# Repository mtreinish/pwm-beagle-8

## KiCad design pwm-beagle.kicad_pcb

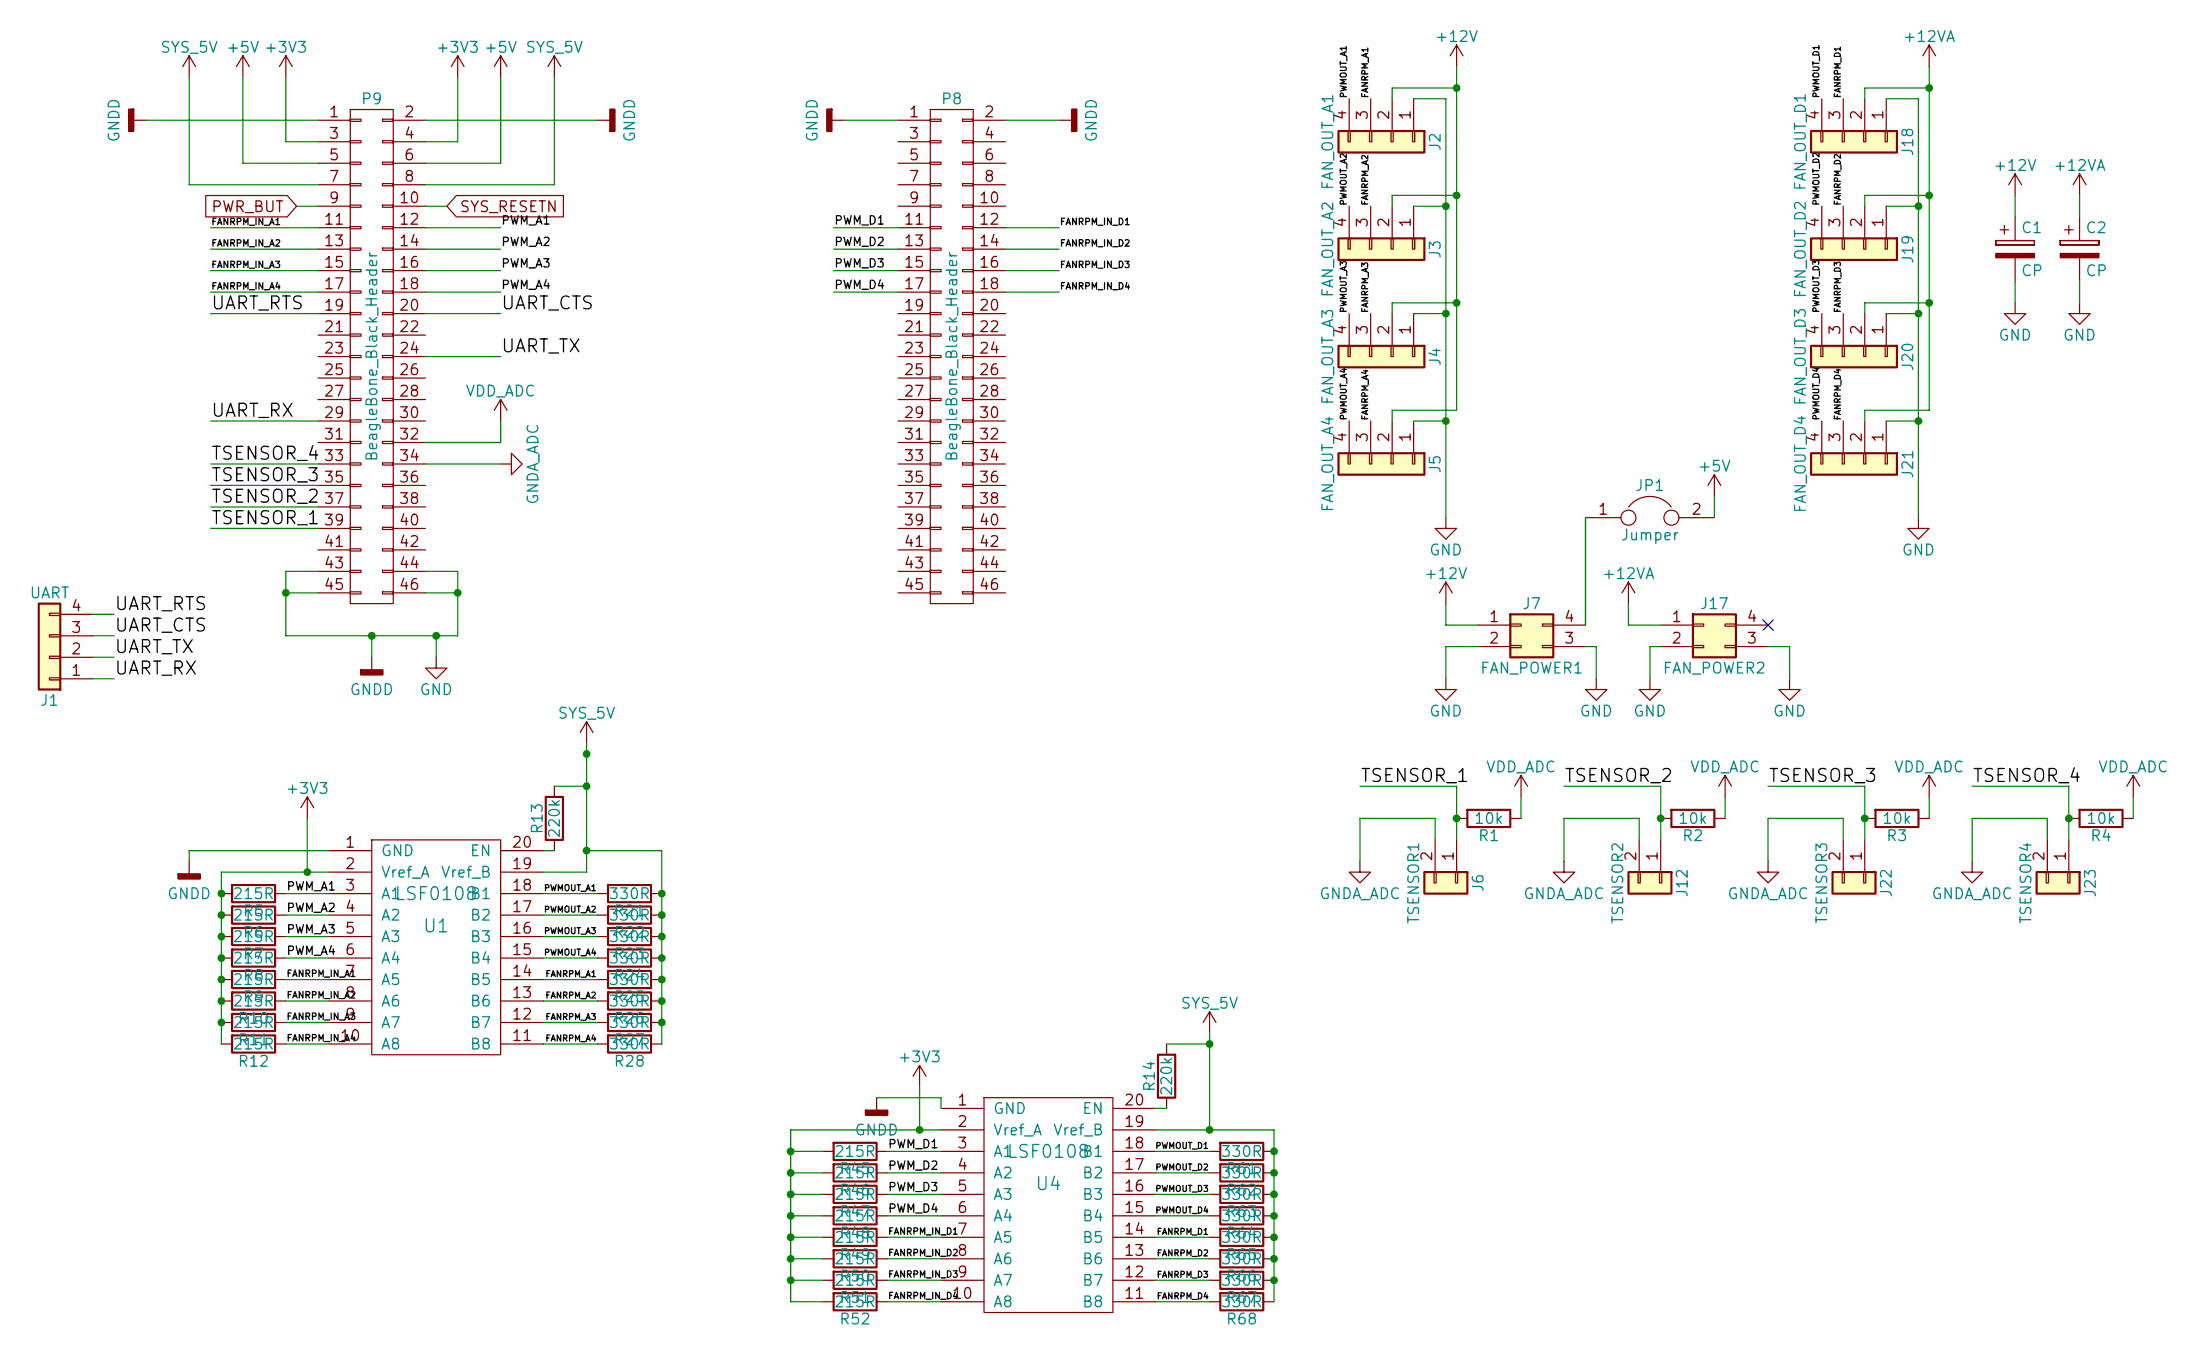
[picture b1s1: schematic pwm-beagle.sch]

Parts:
C1, C2: CP; CP_Elec_5x4.5
J1: UART; Molex_KK-6410-04_04x2.54mm_Straight
J2: FAN_OUT_A1; Molex_KK-6410-04_04x2.54mm_Straight
J3: FAN_OUT_A2; Molex_KK-6410-04_04x2.54mm_Straight
J4: FAN_OUT_A3; Molex_KK-6410-04_04x2.54mm_Straight
J5: FAN_OUT_A4; Molex_KK-6410-04_04x2.54mm_Straight
J6: TSENSOR1; Molex_KK-41791-02_02x3.96mm_Straight
J7: FAN_POWER1; conn_hdd_15-24-4449
J12: TSENSOR2; Molex_KK-41791-02_02x3.96mm_Straight
J17: FAN_POWER2; conn_hdd_15-24-4449
J18: FAN_OUT_D1; Molex_KK-6410-04_04x2.54mm_Straight
J19: FAN_OUT_D2; Molex_KK-6410-04_04x2.54mm_Straight
J20: FAN_OUT_D3; Molex_KK-6410-04_04x2.54mm_Straight
J21: FAN_OUT_D4; Molex_KK-6410-04_04x2.54mm_Straight
J22: TSENSOR3; Molex_KK-41791-02_02x3.96mm_Straight
J23: TSENSOR4; Molex_KK-41791-02_02x3.96mm_Straight
JP1: Jumper; Pin_Header_Straight_1x02_Pitch2.00mm
P8, P9: BeagleBone_Black_Header; Socket_BeagleBone_Black
R1, R2, R3, R4: 10k; R_0805_HandSoldering
R5, R6, R7, R8, R9, R10, R11, R12, R45, R46, R47, R48, R49, R50, R51, R52: 215R; R_0603_HandSoldering
R13, R14: 220k; R_0805_HandSoldering
R21, R22, R23, R24, R25, R26, R27, R28, R61, R62, R63, R64, R65, R66, R67, R68: 330R; R_0603_HandSoldering
U1, U4: LSF0108; SSOP-20

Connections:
+3V3: P9.3, P9.4, R5.2, R6.2, R7.2, R8.2, R9.2, R10.2, R11.2, R12.2, R45.2, R46.2, R47.2, R48.2, R49.2, R50.2, R51.2, R52.2, U1.2 (Vref_A), U4.2 (Vref_A)
+5V: JP1.2, P9.5, P9.6
+12V: C1.1, J2.2, J3.2, J4.2, J5.2, J7.1
+12VA: C2.1, J17.1, J18.2, J19.2, J20.2, J21.2
/FANRPM_A1: J2.3, R25.2, U1.14 (B5)
/FANRPM_A2: J3.3, R26.2, U1.13 (B6)
/FANRPM_A3: J4.3, R27.2, U1.12 (B7)
/FANRPM_A4: J5.3, R28.2, U1.11 (B8)
/FANRPM_D1: J18.3, R65.2, U4.14 (B5)
/FANRPM_D2: J19.3, R66.2, U4.13 (B6)
/FANRPM_D3: J20.3, R67.2, U4.12 (B7)
/FANRPM_D4: J21.3, R68.2, U4.11 (B8)
/FANRPM_IN_A1: P9.11, R9.1, U1.7 (A5)
/FANRPM_IN_A2: P9.13, R10.1, U1.8 (A6)
/FANRPM_IN_A3: P9.15, R11.1, U1.9 (A7)
/FANRPM_IN_A4: P9.17, R12.1, U1.10 (A8)
/FANRPM_IN_D1: P8.12, R49.1, U4.7 (A5)
/FANRPM_IN_D2: P8.14, R50.1, U4.8 (A6)
/FANRPM_IN_D3: P8.16, R51.1, U4.9 (A7)
/FANRPM_IN_D4: P8.18, R52.1, U4.10 (A8)
/PWMOUT_A1: J2.4, R21.2, U1.18 (B1)
/PWMOUT_A2: J3.4, R22.2, U1.17 (B2)
/PWMOUT_A3: J4.4, R23.2, U1.16 (B3)
/PWMOUT_A4: J5.4, R24.2, U1.15 (B4)
/PWMOUT_D1: J18.4, R61.2, U4.18 (B1)
/PWMOUT_D2: J19.4, R62.2, U4.17 (B2)
/PWMOUT_D3: J20.4, R63.2, U4.16 (B3)
/PWMOUT_D4: J21.4, R64.2, U4.15 (B4)
/PWM_A1: P9.12, R5.1, U1.3 (A1)
/PWM_A2: P9.14, R6.1, U1.4 (A2)
/PWM_A3: P9.16, R7.1, U1.5 (A3)
/PWM_A4: P9.18, R8.1, U1.6 (A4)
/PWM_D1: P8.11, R45.1, U4.3 (A1)
/PWM_D2: P8.13, R46.1, U4.4 (A2)
/PWM_D3: P8.15, R47.1, U4.5 (A3)
/PWM_D4: P8.17, R48.1, U4.6 (A4)
/TSENSOR_1: J6.1, P9.39, R1.2
/TSENSOR_2: J12.1, P9.37, R2.2
/TSENSOR_3: J22.1, P9.35, R3.2
/TSENSOR_4: J23.1, P9.33, R4.2
/UART_CTS: J1.3, P9.20
/UART_RTS: J1.4, P9.19
/UART_RX: J1.1, P9.29
/UART_TX: J1.2, P9.24
GND: C1.2, C2.2, J2.1, J3.1, J4.1, J5.1, J7.2, J7.3, J17.2, J17.3, J18.1, J19.1, J20.1, J21.1, P8.1, P8.2, P9.1, P9.2, P9.43, P9.44, P9.45, P9.46, U1.1 (GND), U4.1 (GND)
GNDA_ADC: J6.2, J12.2, J22.2, J23.2, P9.34
unnamed: J7.4, JP1.1
unnamed: R13.1, U1.20 (EN)
unnamed: R14.1, U4.20 (EN)
PWR_BUT: P9.9
SYS_5V: P9.7, P9.8, R13.2, R14.2, R21.1, R22.1, R23.1, R24.1, R25.1, R26.1, R27.1, R28.1, R61.1, R62.1, R63.1, R64.1, R65.1, R66.1, R67.1, R68.1, U1.19 (Vref_B), U4.19 (Vref_B)
SYS_RESETN: P9.10
VDD_ADC: P9.32, R1.1, R2.1, R3.1, R4.1

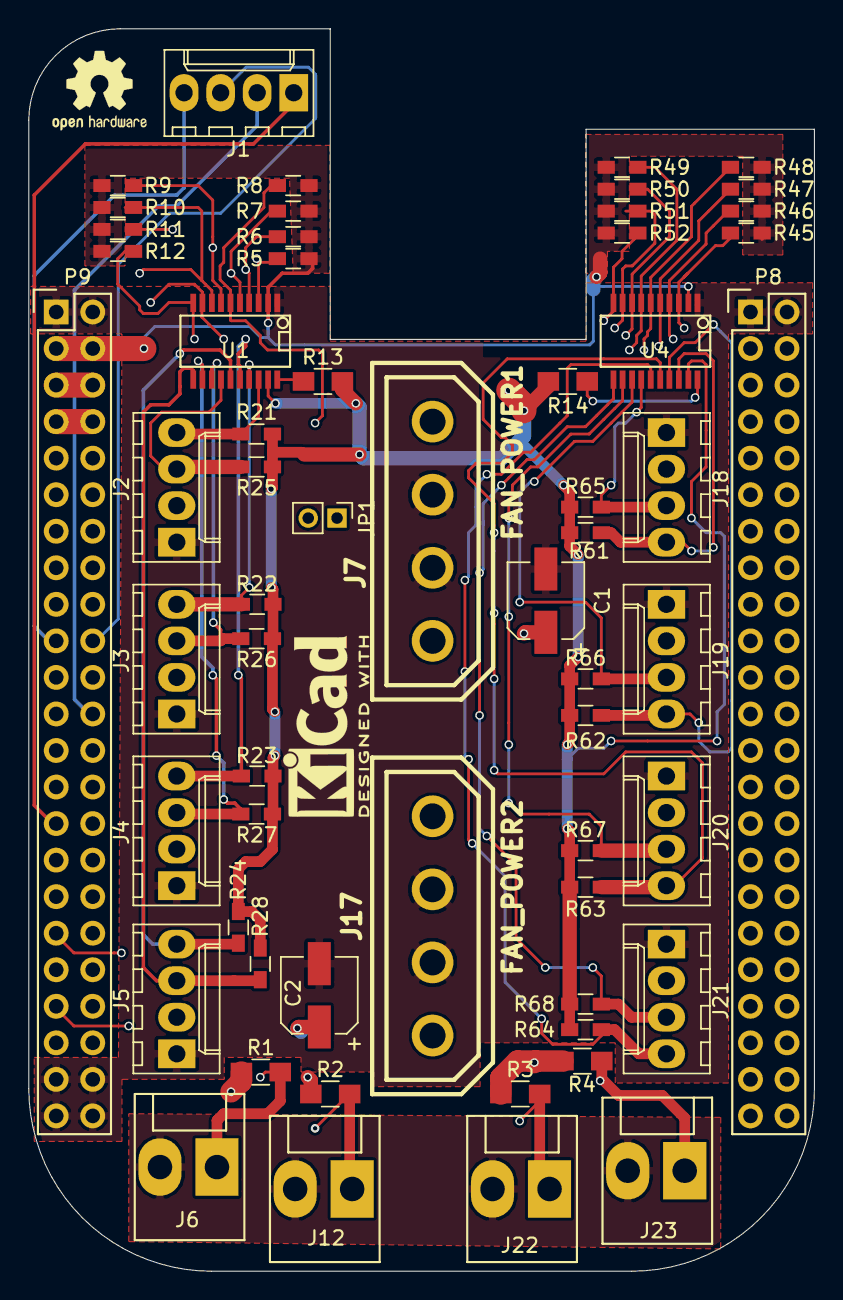
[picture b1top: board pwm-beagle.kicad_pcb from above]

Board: 4 copper layers, 54.6 x 86.4 mm, 60 parts (0 on the bottom side), 51 nets.

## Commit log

2017-10-15 Initial Commit
    This is the start of a beaglebone black based 8 channel pwm fan
    controller. Right now it's just the board design and schematic. While
    everything is wired up at this point it likely will need a bunch of
    refinement. Some of the net paths are less than ideal, it's not clear
    how much that will mater though because PWM fans operate at only ~25kHz.
    In the future software will be added to this repo as well.
2017-10-15 Move silkscreen labels around for clarity
